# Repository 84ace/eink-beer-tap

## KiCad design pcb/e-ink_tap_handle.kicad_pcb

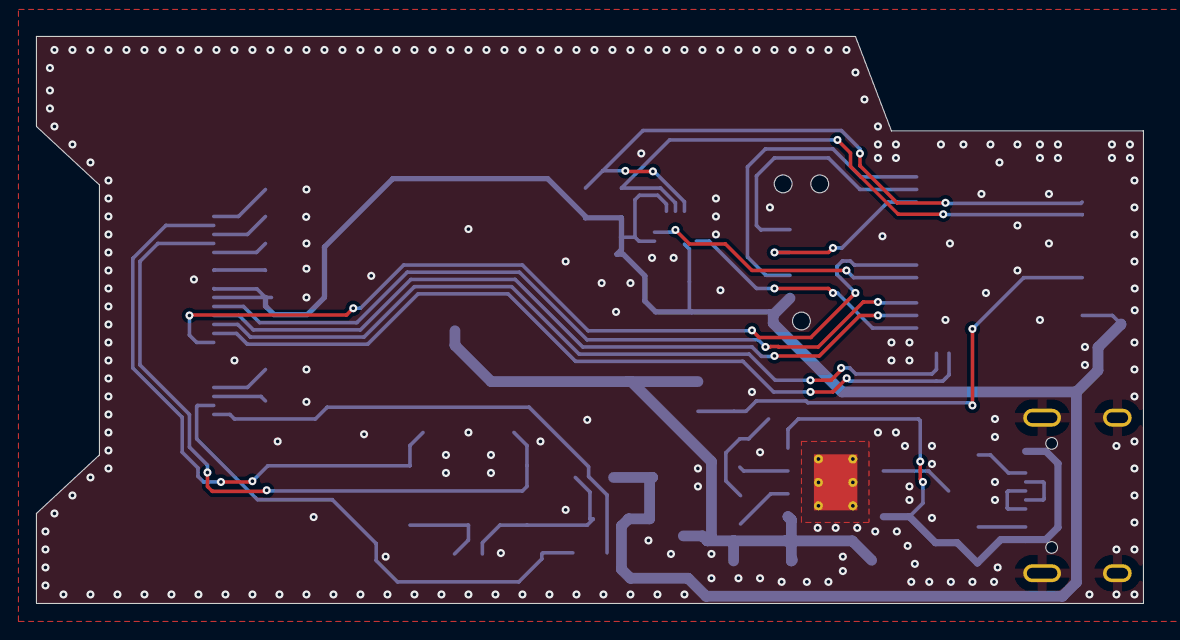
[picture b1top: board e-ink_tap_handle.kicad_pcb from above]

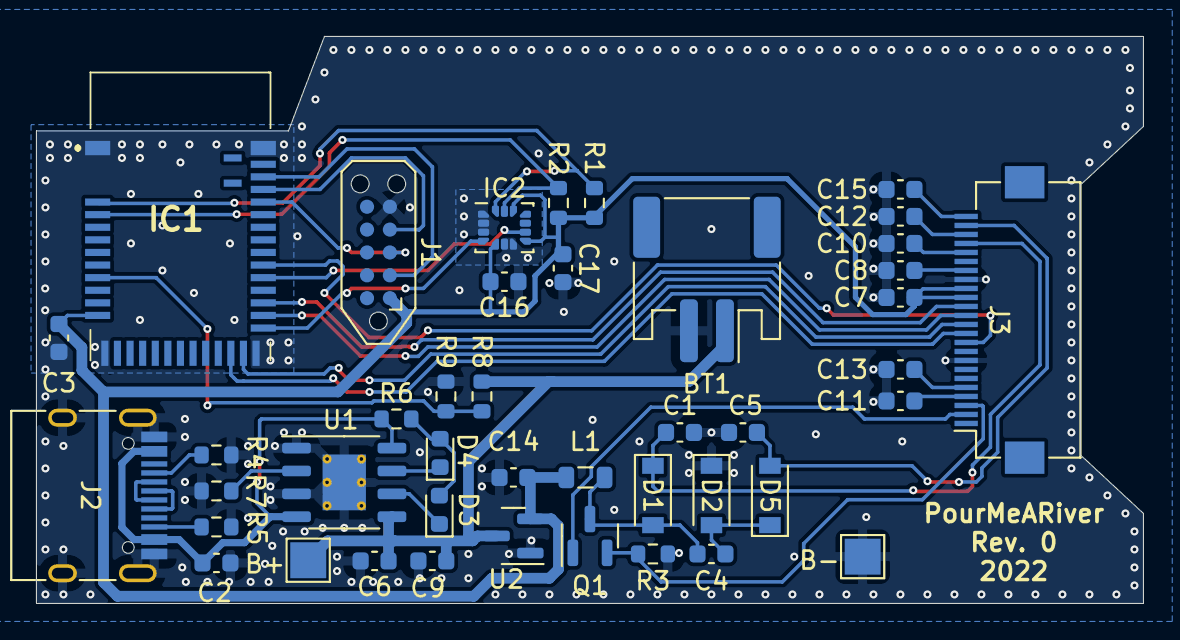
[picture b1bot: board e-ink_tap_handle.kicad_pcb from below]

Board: 2 copper layers, 61.5 x 31.5 mm, 43 parts (43 on the bottom side), 37 nets.

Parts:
BT1: 4.2V; JST_PH_S2B-PH-SM4-TB_1x02-1MP_P2.00mm_Horizontal
C1, C5, C6, C8, C9, C10, C11, C12, C13, C14, C15: 1uF; C_0603_1608Metric
C2, C3, C7, C17: 10uF; C_0603_1608Metric
C4: 4.7uF; C_0603_1608Metric
C16: 100nf; C_0603_1608Metric
D1, D2, D5: MBR0530; D_SOD-123
D3: GLED; LED_0603_1608Metric
D4: RLED; LED_0603_1608Metric
IC1: MDBT42Q-512KV2; MDBT42Q512KV2
IC2: LSM6DSLTR; LGA-14_3x2.5mm_P0.5mm_LayoutBorder3x4y
J1: JTAG_SWD_6; Tag-Connect_TC2050-IDC-NL_2x05_P1.27mm_Vertical
J2: USB_C_Receptacle_USB2.0; USB_C_Receptacle_HRO_TYPE-C-31-M-12
J3: Conn_01x24; Hirose_FH12-24S-0.5SH_1x24-1MP_P0.50mm_Horizontal
L1: 10uH; L_0805_2012Metric
Q1: 2N7002E; SOT-23
R1, R2: 3k; R_0603_1608Metric
R3: 0.47R; R_0603_1608Metric
R4, R5: 5.1k; R_0603_1608Metric
R6, R7: 2k; R_0603_1608Metric
R8: 806k; R_0603_1608Metric
R9: 2M; R_0603_1608Metric
TP1: B+; TestPoint_Pad_2.0x2.0mm
TP2: B-; TestPoint_Pad_2.0x2.0mm
U1: TP4056; HSOP-8-1EP_3.9x4.9mm_P1.27mm_EP2.41x3.1mm_ThermalVias
U2: XC6206PxxxMR; SOT-23

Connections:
+3V3: C3.1, C7.1, C14.1, C16.2, C17.1, IC1.11 (VDD), IC2.5 (VDDIO), IC2.8 (VDD), IC2.12 (CS), J1.1 (VTref), J3.15, J3.16, L1.2, R1.1, R2.1, U2.2 (VO)
BATV: IC1.8 (P0.31), R8.2, R9.1
CS: IC1.23 (P0.10), J3.12
D+: J2.A6 (D+), J2.B6 (D+)
D-: J2.A7 (D-), J2.B7 (D-)
DC: IC1.22 (P0.09), J3.11
GDR: J3.2, Q1.1 (G)
GND: BT1.2 (-), C1.2, C2.2, C3.2, C5.2, C6.2, C7.2, C8.2, C9.2, C10.2, C11.2, C12.2, C13.2, C14.2, C15.2, C16.1, C17.2, D2.1 (K), IC1.1 (GND_1), IC1.12 (GND_2), IC1.24 (GND_3), IC1.39 (GND_4), IC2.1 (SDO/SA0), IC2.2 (SDX), IC2.3 (SCX), IC2.6 (GND_1), IC2.7 (GND_2), J1.5 (GND), J2.A1 (GND), J2.A12 (GND), J2.B1 (GND), J2.B12 (GND), J2.S1 (SHIELD), J3.8, J3.17, R3.2, R4.1, R5.1, R7.2, R9.2, TP2.1, U1.1 (TEMP), U1.3 (GND), U1.9 (PP), U2.1 (GND)
INT1: IC1.25 (P0.11), IC2.4 (INT1)
INT2: IC1.29 (P0.15), IC2.9 (INT2)
MOSI: IC1.27 (P0.13), J3.14
unnamed: BT1.1 (+), C6.1, C9.1, R8.1, TP1.1, U1.5 (BAT), U2.3 (VI)
unnamed: C4.1, D1.2 (A), L1.1, Q1.3 (D)
unnamed: C4.2, D2.2 (A), D5.1 (K)
unnamed: D3.2 (A), D4.2 (A), R6.2
unnamed: D3.1 (K), U1.6 (~STDBY)
unnamed: D4.1 (K), U1.7 (~CHRG)
unnamed: J2.A5 (CC1), R4.2
unnamed: J2.B5 (CC2), R5.2
unnamed: C2.1, J2.A4 (VBUS), J2.A9 (VBUS), J2.B4 (VBUS), J2.B9 (VBUS), R6.1, U1.4 (VCC), U1.8 (CE)
unnamed: C11.1, J3.4
unnamed: C13.1, J3.5
unnamed: C8.1, J3.18
unnamed: C10.1, J3.20
unnamed: C12.1, J3.22
unnamed: C15.1, J3.24
unnamed: R7.1, U1.2 (PROG)
RESE: J3.3, Q1.2 (S), R3.1
SCK: IC1.26 (P0.12), J3.13
SCL: IC1.3 (P0.26), IC2.13 (SCL), R2.2
SDA: IC1.2 (P0.25), IC2.14 (SDA), R1.2
SWCLK: IC1.36 (SWDCLK), J1.4 (SWDCLK/TCK)
SWDIO: IC1.37 (SWDIO), J1.2 (SWDIO/TMS)
VGH: C1.1, D1.1 (K), J3.21
VGL: C5.1, D5.2 (A), J3.23
eRESET: IC1.30 (P0.16), J3.10
~Reset: IC1.35 (P0.21/RESET), J1.3 (~RESET)

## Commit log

2022-05-24 mall changes to PCB 3v3 routing
